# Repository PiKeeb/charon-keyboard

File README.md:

# charon-keyboard
PCB & plate design files for Charon keyboard (originally designed for Charue Design)

A 65% with blocker Keyboard kit originally made and sold by Charue Design. 

## Disclaimers

All the designs and files are provided **"AS IS"** without any warranty or support.

The designs are licensed under [**CC BY-SA 4.0 International Licence**](https://creativecommons.org/licenses/by-sa/4.0/)

## Acknowledgements

Plate design by **Juttcakes**

PCB design by **ILWrites**

Photo by **Charue Design**

## Repository structure
- `/plate` contains the files related to the plate design
- `/pcb` contains the files related to the PCB design

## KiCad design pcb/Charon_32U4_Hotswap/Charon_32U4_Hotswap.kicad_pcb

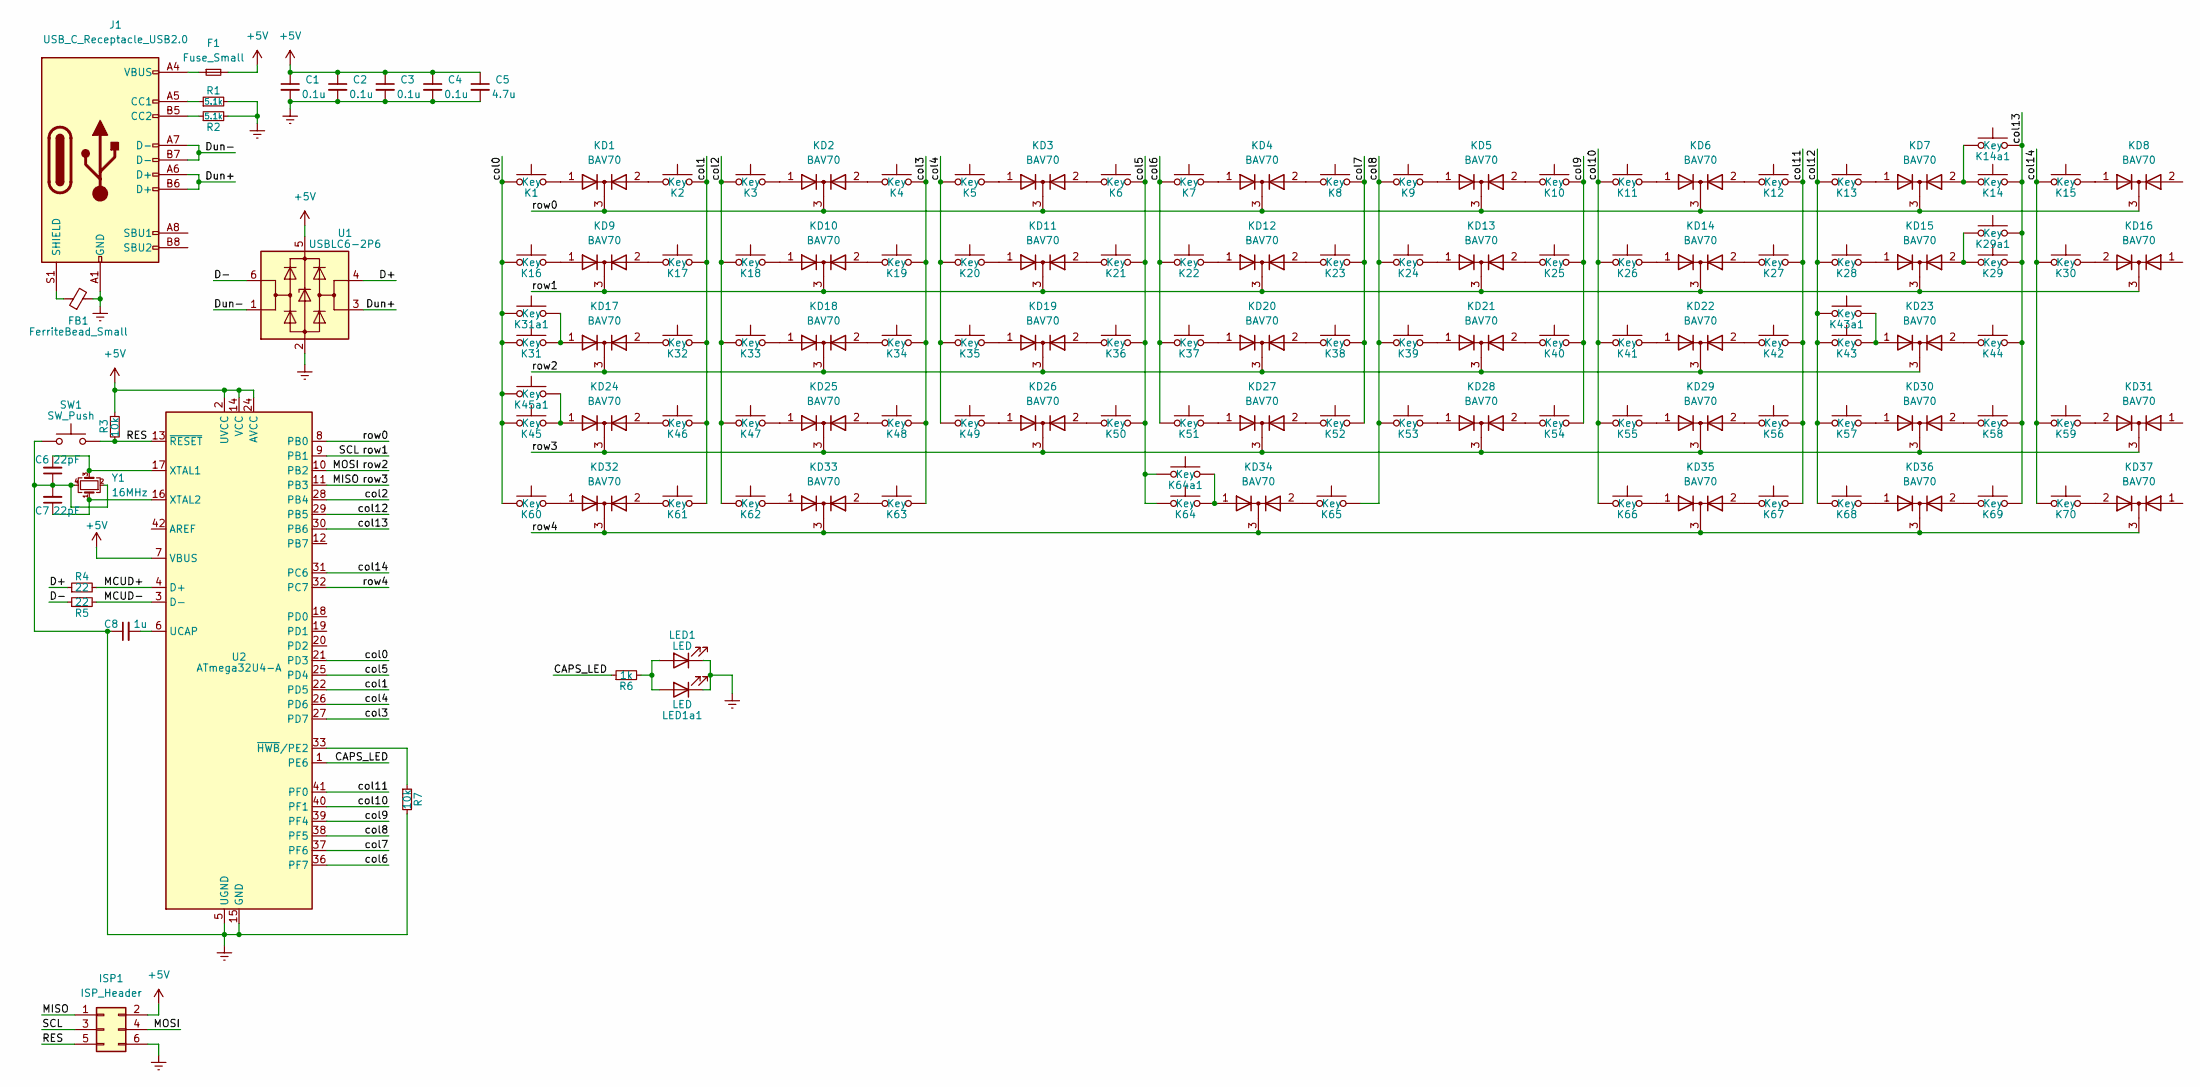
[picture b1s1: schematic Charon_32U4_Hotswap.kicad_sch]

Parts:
C1, C2, C3, C4: 0.1u; C_0603_1608Metric
C5: 4.7u; C_0603_1608Metric
C6, C7: 22pF; C_0603_1608Metric
C8: 1u; C_0603_1608Metric
F1: Fuse_Small; Fuse_0805_2012Metric
FB1: FerriteBead_Small; L_0805_2012Metric
ISP1: ISP_Header; PinHeader_2x03_P2.54mm_Vertical
J1: USB_C_Receptacle_USB2.0; USB_C_Receptacle_HRO_TYPE-C-31-M-12
K1, K2, K3, K4, K5, K6, K7, K8, K9, K10, K11, K12, K13, K14, K15, K17, K18, K19, K20, K21, K22, K23, K24, K25, K26, K27, K28, K29, K29a1, K30, K31, K31a1, K32, K33, K34, K35, K36, K37, K38, K39, K40, K41, K42, K43, K43a1, K44, K45, K46, K47, K48, K49, K50, K51, K52, K53, K54, K55, K56, K57, K58, K59, K60, K61, K62, K63, K66, K67, K68, K69, K70: Key; SW_Cherry_MX_1.00u_PCB
K14a1: Key; SW_Cherry_MX_2.00u_PCB
K16: Key; SW_Cherry_MX_1.50u_PCB
K45a1: Key; SW_Cherry_MX_2.25u_PCB
K64, K64a1: Key; SW_Cherry_MX_2.25u_PCB_NoStab
K65: Key; SW_Cherry_MX_2.75u_PCB_NoStab
KD1, KD2, KD3, KD4, KD5, KD6, KD7, KD8, KD9, KD10, KD11, KD12, KD13, KD14, KD15, KD16, KD17, KD18, KD19, KD20, KD21, KD22, KD23, KD24, KD25, KD26, KD27, KD28, KD29, KD30, KD31, KD32, KD33, KD34, KD35, KD36, KD37: BAV70; SOT-23
LED1, LED1a1: LED; PinSocket_2x01_P2.54mm_Vertical
R1, R2: 5.1k; R_0603_1608Metric
R3, R7: 10k; R_0603_1608Metric
R4, R5: 22; R_0603_1608Metric
R6: 1k; R_0603_1608Metric
SW1: SW_Push; SW_SPST_TL3342
U1: USBLC6-2P6; SOT-666
U2: ATmega32U4-A; TQFP-44_10x10mm_P0.8mm
Y1: 16MHz; Crystal_SMD_3225-4Pin_3.2x2.5mm

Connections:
+5V: C1.1, C2.1, C3.1, C4.1, C5.1, F1.2, ISP1.2, R3.1, U1.5 (VBUS), U2.2 (UVCC), U2.7 (VBUS), U2.14 (VCC), U2.24 (AVCC), U2.34 (VCC), U2.44 (AVCC)
/CAPS_LED: R6.1, U2.1 (PE6)
/D+: R4.1, U1.4 (I/O2)
/D-: R5.1, U1.6 (I/O1)
/Dun+: J1.A6 (D+), J1.B6 (D+), U1.3 (I/O2)
/Dun-: J1.A7 (D-), J1.B7 (D-), U1.1 (I/O1)
/MCUD+: R4.2, U2.4 (D+)
/MCUD-: R5.2, U2.3 (D-)
/MISO: ISP1.1, KD24.3 (K), KD25.3 (K), KD26.3 (K), KD27.3 (K), KD28.3 (K), KD29.3 (K), KD30.3 (K), KD31.3 (K), U2.11 (PB3)
/MOSI: ISP1.4, KD17.3 (K), KD18.3 (K), KD19.3 (K), KD20.3 (K), KD21.3 (K), KD22.3 (K), KD23.3 (K), U2.10 (PB2)
/RES: ISP1.5, R3.2, SW1.2, U2.13 (~RESET)
/SCL: ISP1.3, KD9.3 (K), KD10.3 (K), KD11.3 (K), KD12.3 (K), KD13.3 (K), KD14.3 (K), KD15.3 (K), KD16.3 (K), U2.9 (PB1)
/col0: K1.1, K16.1, K31.2, K31a1.1, K45.2, K45a1.1, K60.1, U2.21 (PD3)
/col1: K2.2, K17.2, K32.2, K46.2, K61.2, U2.22 (PD5)
/col2: K3.1, K18.1, K33.1, K47.1, K62.1, U2.28 (PB4)
/col3: K4.2, K19.2, K34.2, K48.2, K63.2, U2.27 (PD7)
/col4: K5.1, K20.1, K35.1, K49.1, U2.26 (PD6)
/col5: K6.2, K21.2, K36.2, K50.2, K64.1, K64a1.1, U2.25 (PD4)
/col6: K7.1, K22.1, K37.1, K51.1, U2.36 (PF7)
/col7: K8.1, K23.2, K38.2, K52.2, U2.37 (PF6)
/col8: K9.2, K24.1, K39.1, K53.1, K65.2, U2.38 (PF5)
/col9: K10.2, K25.2, K40.2, K54.2, U2.39 (PF4)
/col10: K11.1, K26.1, K41.1, K55.1, K66.1, U2.40 (PF1)
/col11: K12.2, K27.2, K42.2, K56.2, K67.2, U2.41 (PF0)
/col12: K13.1, K28.1, K43.1, K43a1.2, K57.1, K68.1, U2.29 (PB5)
/col13: K14.1, K14a1.2, K29.2, K29a1.2, K44.2, K58.2, K69.2, U2.30 (PB6)
/col14: K15.2, K30.2, K59.2, K70.2, U2.31 (PC6)
/row0: KD1.3 (K), KD2.3 (K), KD3.3 (K), KD4.3 (K), KD5.3 (K), KD6.3 (K), KD7.3 (K), KD8.3 (K), U2.8 (PB0)
/row4: KD32.3 (K), KD33.3 (K), KD34.3 (K), KD35.3 (K), KD36.3 (K), KD37.3 (K), U2.32 (PC7)
Earth: C1.2, C2.2, C3.2, C4.2, C5.2, C6.1, C7.2, C8.1, FB1.2, ISP1.6, J1.A1 (GND), J1.A12 (GND), J1.B1 (GND), J1.B12 (GND), LED1.1 (K), LED1a1.1 (K), R1.2, R2.2, R7.2, SW1.1, U1.2 (GND), U2.5 (UGND), U2.15 (GND), U2.23 (GND), U2.35 (GND), U2.43 (GND), Y1.2, Y1.4
unnamed: C6.2, U2.17 (XTAL1), Y1.3
unnamed: C7.1, U2.16 (XTAL2), Y1.1
unnamed: C8.2, U2.6 (UCAP)
unnamed: F1.1, J1.A4 (VBUS), J1.A9 (VBUS), J1.B4 (VBUS), J1.B9 (VBUS)
unnamed: FB1.1, J1.S1 (SHIELD)
unnamed: J1.A5 (CC1), R1.1
unnamed: J1.B5 (CC2), R2.1
unnamed: K1.2, KD1.1 (A)
unnamed: K2.1, KD1.2 (A)
unnamed: K3.2, KD2.1 (A)
unnamed: K4.1, KD2.2 (A)
unnamed: K5.2, KD3.1 (A)
unnamed: K6.1, KD3.2 (A)
unnamed: K7.2, KD4.1 (A)
unnamed: K8.2, KD4.2 (A)
unnamed: K9.1, KD5.1 (A)
unnamed: K10.1, KD5.2 (A)
unnamed: K11.2, KD6.1 (A)
unnamed: K12.1, KD6.2 (A)
unnamed: K13.2, KD7.1 (A)
unnamed: K14.2, K14a1.1, KD7.2 (A)
unnamed: K15.1, KD8.1 (A)
unnamed: K16.2, KD9.1 (A)
unnamed: K17.1, KD9.2 (A)
unnamed: K18.2, KD10.1 (A)
unnamed: K19.1, KD10.2 (A)
unnamed: K20.2, KD11.1 (A)
unnamed: K21.1, KD11.2 (A)
unnamed: K22.2, KD12.1 (A)
unnamed: K23.1, KD12.2 (A)
unnamed: K24.2, KD13.1 (A)
unnamed: K25.1, KD13.2 (A)
unnamed: K26.2, KD14.1 (A)
unnamed: K27.1, KD14.2 (A)
unnamed: K28.2, KD15.1 (A)
unnamed: K29.1, K29a1.1, KD15.2 (A)
unnamed: K30.1, KD16.2 (A)
unnamed: K31.1, K31a1.2, KD17.1 (A)
unnamed: K32.1, KD17.2 (A)
unnamed: K33.2, KD18.1 (A)
unnamed: K34.1, KD18.2 (A)
unnamed: K35.2, KD19.1 (A)
unnamed: K36.1, KD19.2 (A)
unnamed: K37.2, KD20.1 (A)
unnamed: K38.1, KD20.2 (A)
unnamed: K39.2, KD21.1 (A)
unnamed: K40.1, KD21.2 (A)
unnamed: K41.2, KD22.1 (A)
unnamed: K42.1, KD22.2 (A)
unnamed: K43.2, K43a1.1, KD23.1 (A)
unnamed: K44.1, KD23.2 (A)
unnamed: K45.1, K45a1.2, KD24.1 (A)
unnamed: K46.1, KD24.2 (A)
unnamed: K47.2, KD25.1 (A)
unnamed: K48.1, KD25.2 (A)
unnamed: K49.2, KD26.1 (A)
unnamed: K50.1, KD26.2 (A)
unnamed: K51.2, KD27.1 (A)
unnamed: K52.1, KD27.2 (A)
unnamed: K53.2, KD28.1 (A)
unnamed: K54.1, KD28.2 (A)
unnamed: K55.2, KD29.1 (A)
unnamed: K56.1, KD29.2 (A)
unnamed: K57.2, KD30.1 (A)
unnamed: K58.1, KD30.2 (A)
unnamed: K59.1, KD31.2 (A)
unnamed: K60.2, KD32.1 (A)
unnamed: K61.1, KD32.2 (A)
unnamed: K62.2, KD33.1 (A)
unnamed: K63.1, KD33.2 (A)
unnamed: K64.2, K64a1.2, KD34.1 (A)
unnamed: K65.1, KD34.2 (A)
unnamed: K66.2, KD35.1 (A)
unnamed: K67.1, KD35.2 (A)
unnamed: K68.2, KD36.1 (A)
unnamed: K69.1, KD36.2 (A)
unnamed: K70.1, KD37.2 (A)
unnamed: LED1.2 (A), LED1a1.2 (A), R6.2
unnamed: R7.1, U2.33 (~HWB/PE2)

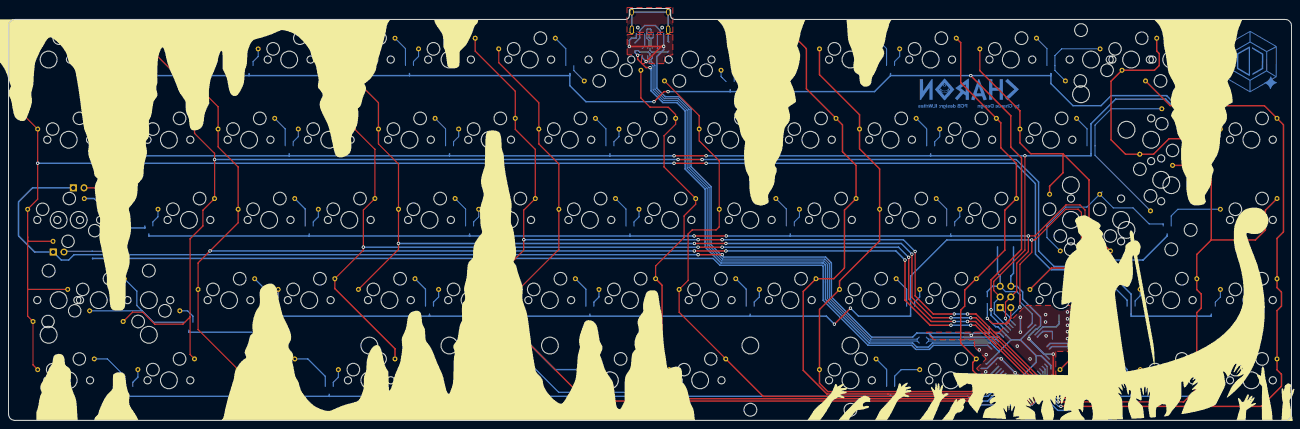
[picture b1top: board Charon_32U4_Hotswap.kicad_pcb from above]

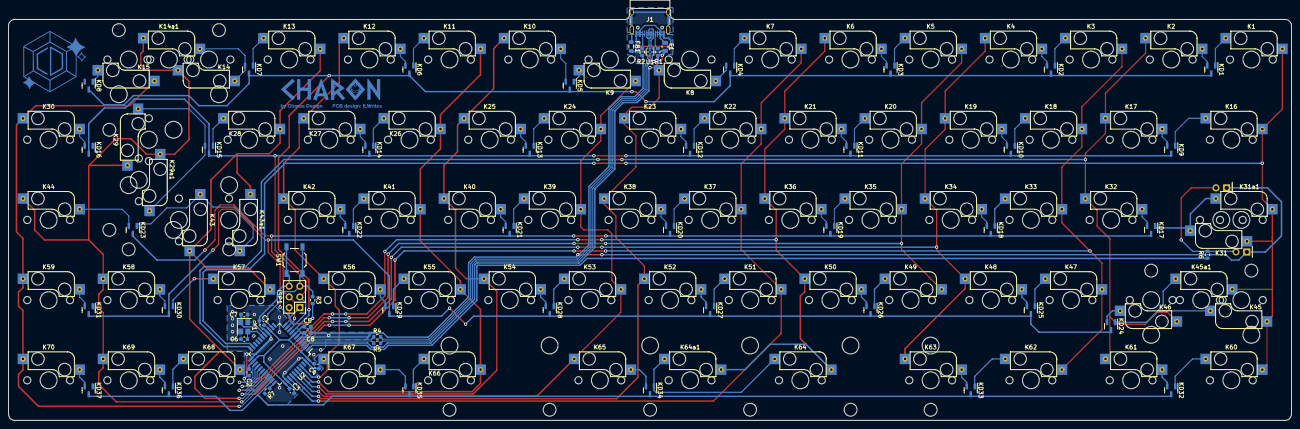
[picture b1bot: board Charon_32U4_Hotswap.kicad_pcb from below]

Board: 2 copper layers, 304.8 x 97.9 mm, 141 parts (138 on the bottom side), 109 nets.

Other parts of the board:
>NAME: >VALUE; Mx_Stab_225
>NAME#2: >VALUE; Mx_Stab_275
>NAME#3: >VALUE; Mx_Stab_225

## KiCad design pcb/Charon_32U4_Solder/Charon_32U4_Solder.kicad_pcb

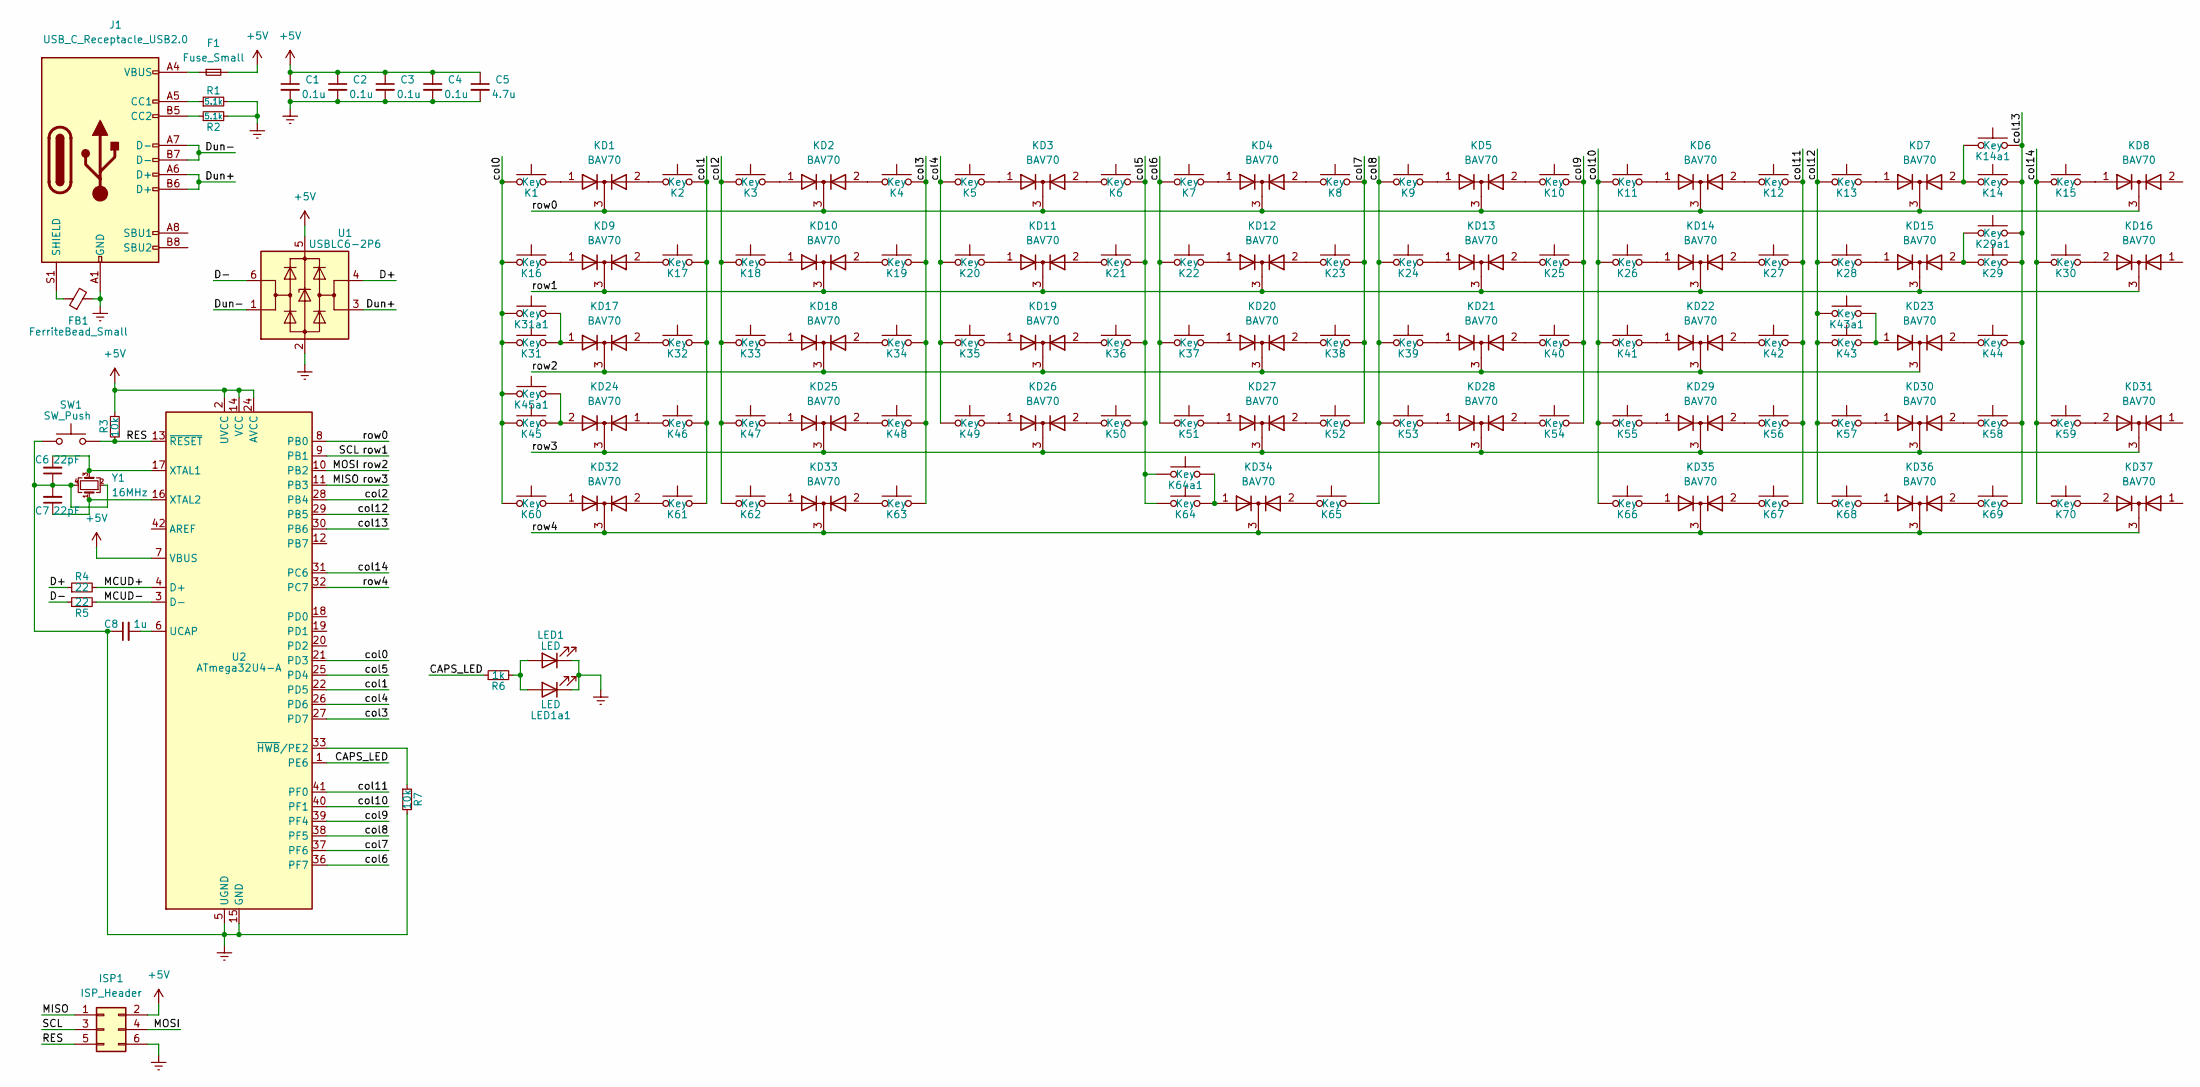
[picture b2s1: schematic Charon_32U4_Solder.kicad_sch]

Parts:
C1, C2, C3, C4: 0.1u; C_0603_1608Metric
C5: 4.7u; C_0603_1608Metric
C6, C7: 22pF; C_0603_1608Metric
C8: 1u; C_0603_1608Metric
F1: Fuse_Small; Fuse_0805_2012Metric
FB1: FerriteBead_Small; L_0805_2012Metric
ISP1: ISP_Header; PinHeader_2x03_P2.54mm_Vertical
J1: USB_C_Receptacle_USB2.0; USB_C_Receptacle_HRO_TYPE-C-31-M-12
K1, K2, K3, K4, K5, K6, K7, K8, K9, K10, K11, K12, K13, K14, K15, K17, K18, K19, K20, K21, K22, K23, K24, K25, K26, K27, K28, K29, K29a1, K30, K31, K31a1, K32, K33, K34, K35, K36, K37, K38, K39, K40, K41, K42, K43, K43a1, K44, K45, K46, K47, K48, K49, K50, K51, K52, K53, K54, K55, K56, K57, K58, K59, K60, K61, K62, K63, K66, K67, K68, K69, K70: Key; SW_Cherry_MX_1.00u_PCB
K14a1: Key; SW_Cherry_MX_2.00u_PCB
K16: Key; SW_Cherry_MX_1.50u_PCB
K45a1: Key; SW_Cherry_MX_2.25u_PCB
K64, K64a1: Key; SW_Cherry_MX_2.25u_PCB_NoStab
K65: Key; SW_Cherry_MX_2.75u_PCB_NoStab
KD1, KD2, KD3, KD4, KD5, KD6, KD7, KD8, KD9, KD10, KD11, KD12, KD13, KD14, KD15, KD16, KD17, KD18, KD19, KD20, KD21, KD22, KD23, KD24, KD25, KD26, KD27, KD28, KD29, KD30, KD31, KD32, KD33, KD34, KD35, KD36, KD37: BAV70; SOT-23
LED1, LED1a1: LED; PinSocket_2x01_P2.54mm_Vertical
R1, R2: 5.1k; R_0603_1608Metric
R3, R7: 10k; R_0603_1608Metric
R4, R5: 22; R_0603_1608Metric
R6: 1k; R_0603_1608Metric
SW1: SW_Push; SW_SPST_TL3342
U1: USBLC6-2P6; SOT-666
U2: ATmega32U4-A; TQFP-44_10x10mm_P0.8mm
Y1: 16MHz; Crystal_SMD_3225-4Pin_3.2x2.5mm

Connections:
+5V: C1.1, C2.1, C3.1, C4.1, C5.1, F1.2, ISP1.2, R3.1, U1.5 (VBUS), U2.2 (UVCC), U2.7 (VBUS), U2.14 (VCC), U2.24 (AVCC), U2.34 (VCC), U2.44 (AVCC)
/CAPS_LED: R6.1, U2.1 (PE6)
/D+: R4.1, U1.4 (I/O2)
/D-: R5.1, U1.6 (I/O1)
/Dun+: J1.A6 (D+), J1.B6 (D+), U1.3 (I/O2)
/Dun-: J1.A7 (D-), J1.B7 (D-), U1.1 (I/O1)
/MCUD+: R4.2, U2.4 (D+)
/MCUD-: R5.2, U2.3 (D-)
/MISO: ISP1.1, KD24.3 (K), KD25.3 (K), KD26.3 (K), KD27.3 (K), KD28.3 (K), KD29.3 (K), KD30.3 (K), KD31.3 (K), U2.11 (PB3)
/MOSI: ISP1.4, KD17.3 (K), KD18.3 (K), KD19.3 (K), KD20.3 (K), KD21.3 (K), KD22.3 (K), KD23.3 (K), U2.10 (PB2)
/RES: ISP1.5, R3.2, SW1.2, U2.13 (~RESET)
/SCL: ISP1.3, KD9.3 (K), KD10.3 (K), KD11.3 (K), KD12.3 (K), KD13.3 (K), KD14.3 (K), KD15.3 (K), KD16.3 (K), U2.9 (PB1)
/col0: K1.2, K16.2, K31.2, K31a1.2, K45.2, K45a1.2, K60.2, U2.21 (PD3)
/col1: K2.1, K17.1, K32.1, K46.1, K61.1, U2.22 (PD5)
/col2: K3.2, K18.2, K33.2, K47.2, K62.2, U2.28 (PB4)
/col3: K4.1, K19.1, K34.1, K48.1, K63.1, U2.27 (PD7)
/col4: K5.2, K20.2, K35.2, K49.2, U2.26 (PD6)
/col5: K6.1, K21.1, K36.1, K50.1, K64.2, K64a1.2, U2.25 (PD4)
/col6: K7.2, K22.2, K37.2, K51.2, U2.36 (PF7)
/col7: K8.1, K23.1, K38.1, K52.1, U2.37 (PF6)
/col8: K9.2, K24.2, K39.2, K53.2, K65.1, U2.38 (PF5)
/col9: K10.1, K25.1, K40.1, K54.1, U2.39 (PF4)
/col10: K11.2, K26.2, K41.2, K55.2, K66.2, U2.40 (PF1)
/col11: K12.1, K27.1, K42.1, K56.1, K67.1, U2.41 (PF0)
/col12: K13.2, K28.2, K43.2, K43a1.2, K57.2, K68.2, U2.29 (PB5)
/col13: K14.1, K14a1.1, K29.2, K29a1.1, K44.1, K58.1, K69.1, U2.30 (PB6)
/col14: K15.2, K30.1, K59.1, K70.1, U2.31 (PC6)
/row0: KD1.3 (K), KD2.3 (K), KD3.3 (K), KD4.3 (K), KD5.3 (K), KD6.3 (K), KD7.3 (K), KD8.3 (K), U2.8 (PB0)
/row4: KD32.3 (K), KD33.3 (K), KD34.3 (K), KD35.3 (K), KD36.3 (K), KD37.3 (K), U2.32 (PC7)
unnamed: C6.2, U2.17 (XTAL1), Y1.3
unnamed: C7.1, U2.16 (XTAL2), Y1.1
unnamed: C8.2, U2.6 (UCAP)
unnamed: F1.1, J1.A4 (VBUS), J1.A9 (VBUS), J1.B4 (VBUS), J1.B9 (VBUS)
unnamed: FB1.1, J1.S1 (SHIELD)
unnamed: J1.A5 (CC1), R1.1
unnamed: J1.B5 (CC2), R2.1
unnamed: K1.1, KD1.1 (A)
unnamed: K2.2, KD1.2 (A)
unnamed: K3.1, KD2.1 (A)
unnamed: K4.2, KD2.2 (A)
unnamed: K5.1, KD3.1 (A)
unnamed: K6.2, KD3.2 (A)
unnamed: K7.1, KD4.1 (A)
unnamed: K8.2, KD4.2 (A)
unnamed: K9.1, KD5.1 (A)
unnamed: K10.2, KD5.2 (A)
unnamed: K11.1, KD6.1 (A)
unnamed: K12.2, KD6.2 (A)
unnamed: K13.1, KD7.1 (A)
unnamed: K14.2, K14a1.2, KD7.2 (A)
unnamed: K15.1, KD8.1 (A)
unnamed: K16.1, KD9.1 (A)
unnamed: K17.2, KD9.2 (A)
unnamed: K18.1, KD10.1 (A)
unnamed: K19.2, KD10.2 (A)
unnamed: K20.1, KD11.1 (A)
unnamed: K21.2, KD11.2 (A)
unnamed: K22.1, KD12.1 (A)
unnamed: K23.2, KD12.2 (A)
unnamed: K24.1, KD13.1 (A)
unnamed: K25.2, KD13.2 (A)
unnamed: K26.1, KD14.1 (A)
unnamed: K27.2, KD14.2 (A)
unnamed: K28.1, KD15.1 (A)
unnamed: K29.1, K29a1.2, KD15.2 (A)
unnamed: K30.2, KD16.2 (A)
unnamed: K31.1, K31a1.1, KD17.1 (A)
unnamed: K32.2, KD17.2 (A)
unnamed: K33.1, KD18.1 (A)
unnamed: K34.2, KD18.2 (A)
unnamed: K35.1, KD19.1 (A)
unnamed: K36.2, KD19.2 (A)
unnamed: K37.1, KD20.1 (A)
unnamed: K38.2, KD20.2 (A)
unnamed: K39.1, KD21.1 (A)
unnamed: K40.2, KD21.2 (A)
unnamed: K41.1, KD22.1 (A)
unnamed: K42.2, KD22.2 (A)
unnamed: K43.1, K43a1.1, KD23.1 (A)
unnamed: K44.2, KD23.2 (A)
unnamed: K45.1, K45a1.1, KD24.2 (A)
unnamed: K46.2, KD24.1 (A)
unnamed: K47.1, KD25.1 (A)
unnamed: K48.2, KD25.2 (A)
unnamed: K49.1, KD26.1 (A)
unnamed: K50.2, KD26.2 (A)
unnamed: K51.1, KD27.1 (A)
unnamed: K52.2, KD27.2 (A)
unnamed: K53.1, KD28.1 (A)
unnamed: K54.2, KD28.2 (A)
unnamed: K55.1, KD29.1 (A)
unnamed: K56.2, KD29.2 (A)
unnamed: K57.1, KD30.1 (A)
unnamed: K58.2, KD30.2 (A)
unnamed: K59.2, KD31.2 (A)
unnamed: K60.1, KD32.1 (A)
unnamed: K61.2, KD32.2 (A)
unnamed: K62.1, KD33.1 (A)
unnamed: K63.2, KD33.2 (A)
unnamed: K64.1, K64a1.1, KD34.1 (A)
unnamed: K65.2, KD34.2 (A)
unnamed: K66.1, KD35.1 (A)
unnamed: K67.2, KD35.2 (A)
unnamed: K68.1, KD36.1 (A)
unnamed: K69.2, KD36.2 (A)
unnamed: K70.2, KD37.2 (A)
unnamed: LED1.2 (A), LED1a1.2 (A), R6.2
unnamed: R7.1, U2.33 (~HWB/PE2)

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
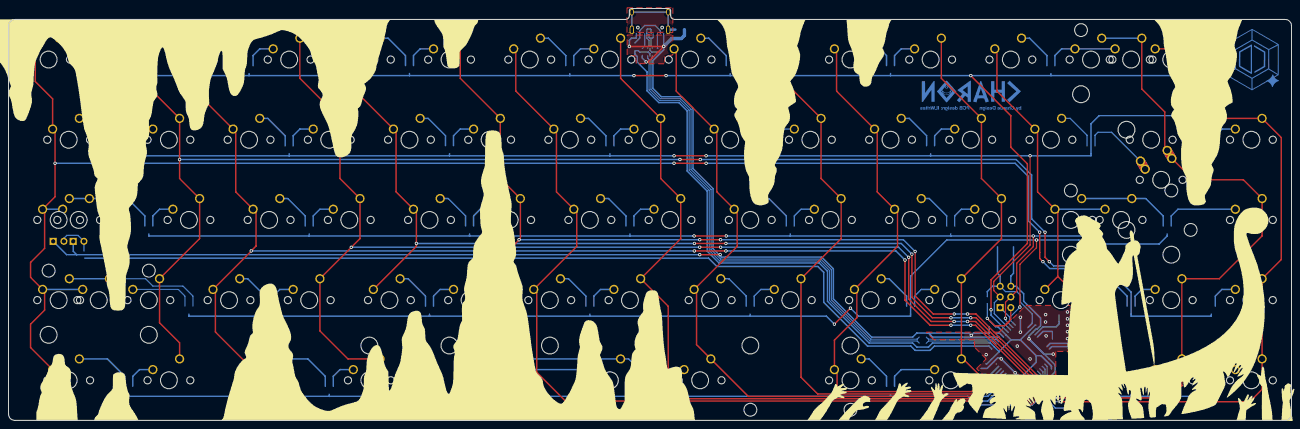
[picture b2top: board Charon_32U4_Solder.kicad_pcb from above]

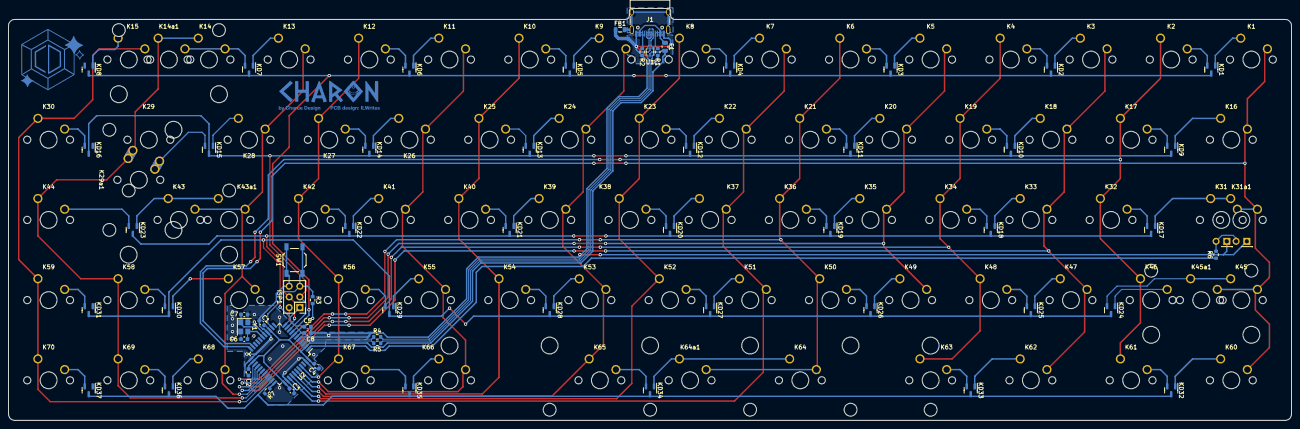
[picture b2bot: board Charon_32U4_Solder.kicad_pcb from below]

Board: 2 copper layers, 304.8 x 97.9 mm, 141 parts (62 on the bottom side), 109 nets.

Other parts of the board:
>NAME: >VALUE; Mx_Stab_225
>NAME#2: >VALUE; Mx_Stab_275
>NAME#3: >VALUE; Mx_Stab_225

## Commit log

2023-01-05 Initial files commit

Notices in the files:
README.md:
creativecommons-by-sa
